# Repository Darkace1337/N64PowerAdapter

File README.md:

# N64PowerAdapter

A modern, universal replacement power supply for the Nintendo 64 using readily available, high-quality power modules.

This project includes the PCB design, schematic, and 3D-printable enclosure required to build a replacement for the original Nintendo 64 power supply. The supply accepts universal AC mains through an IEC C8 connector and provides the 12 V and 3.3 V rails required by the N64 through the original 6-pin power connector.

The design uses TRACO Power modules for the AC/DC and DC/DC conversion, keeping the power circuitry simple while providing an isolated and compact replacement for aging original power supplies.

## Requirements

**A sacrificial Nintendo 64 power adapter (official or third-party) is required for the original 6-pin console connector.**

The connector must be removed from the donor power supply and installed onto the replacement PCB.

## Bill of Materials

| Reference | Qty | Manufacturer | Part Number | Description |
|:---|---:|:---|:---|:---|
| PS1 | 1 | TRACO Power | TEL 10-2410WI | 10 W isolated DC/DC converter, 9–36 V input, 3.3 V / 2.7 A output |
| PS2 | 1 | TRACO Power | TMPW 25-112 | 25 W AC/DC converter, 12 V / 2.083 A output |
| C1 | 1 | KYOCERA AVX | TAJD476K025SNJ | 47 µF, 25 V, 10% tantalum capacitor |
| C2, C4 | 2 | Vishay | 05007-BR104AKU-J | 0.1 µF, 25 V, 10% MLCC |
| C5 | 1 | Vishay | 592D477X96R3C2T20H | 470 µF, 6.3 V, 10% tantalum capacitor |
| F1 | 1 | Eaton | C310T-SC-2-5-R-TR1 | 2.5 A, 250 V ceramic cartridge fuse |
| J1 | 1 | — | Amazon | C8 Panel Mount Plug, flange mount type |
| J3 | 1 | Nintendo / Donor PSU | — | Original N64 6-pin power connector |
| Screws-A | 3 | - | Amazon | M3 x 5 mm Button-head machine screws
| Screws-B | 4 | - | Amazon | M3 x 6 mm Countersunk self tapping screws
| Thread Inserts| 2 | - | Amazon | M3 x 4 mm Heat-set insets

## Project Files

* Schematic and PCB design
* Gerber/manufacturing files
* 3D-printable enclosure
* Reference photos of the assembled prototype

## Prototype / Revision Note

**The photos shown below are of an earlier prototype revision.**

The PCB used in the photographed prototype required a small section of the board to be manually cut for proper mechanical fitment. The PCB layout has since been revised to correct this interference.

The current revision is intended to fit without this modification, but has not yet been physically verified in the same configuration shown in the photos.

## Photos

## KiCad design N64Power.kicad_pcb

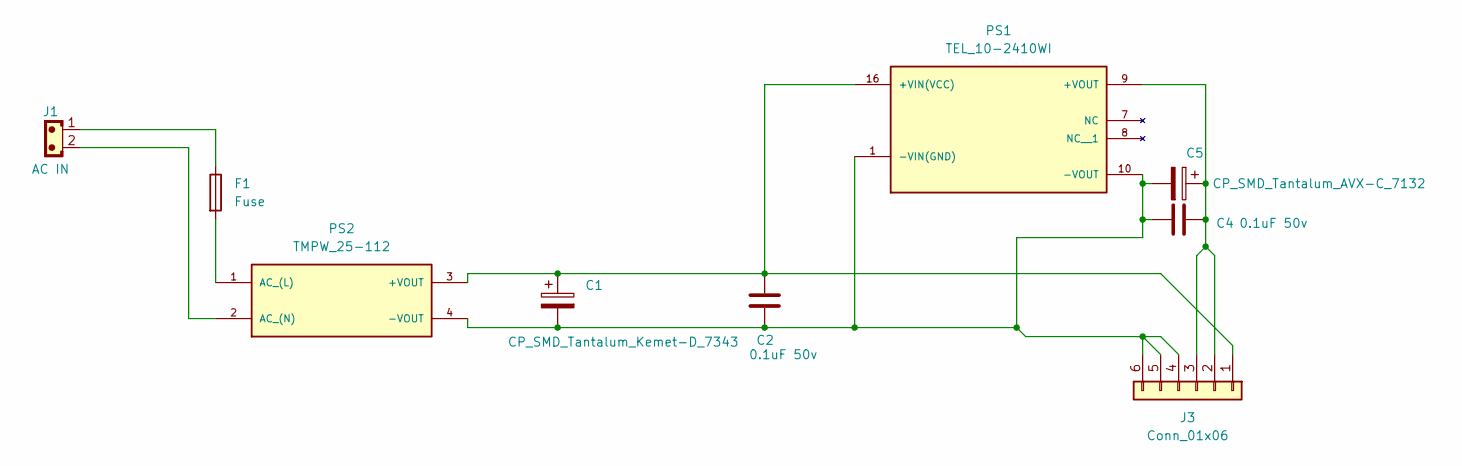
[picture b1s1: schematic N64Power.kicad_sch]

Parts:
C1: CP_SMD_Tantalum_Kemet-D_7343; CP_EIA-7343-31_Kemet-D
C2, C4: 0.1uF 50v; C_1206_3216Metric_Pad1.33x1.80mm_HandSolder
C5: CP_SMD_Tantalum_AVX-C_7132; CP_EIA-7132-28_AVX-C
F1: Fuse; FUSE_0683G2500-01
J1: AC IN; SolderWire-0.75sqmm_1x02_P4.8mm_D1.25mm_OD2.3mm
J3: Conn_01x06; n64ribbon
PS1: TEL_10-2410WI; CONV_TEL_10-2410WI; PARTREV June 16, 2021
PS2: TMPW_25-112; CONV_TMPW_25-112; PARTREV April 20,2021

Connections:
+3.3V: C4.2, C5.1, J3.2, J3.3, PS1.9 (+VOUT)
+12V: C1.1, C2.1, J3.1, PS1.16 (+VIN(VCC)), PS2.3 (+VOUT)
GND: C1.2, C2.2, C4.1, C5.2, J3.4, J3.5, J3.6, PS1.1 (-VIN(GND)), PS1.10 (-VOUT), PS2.4 (-VOUT)
unnamed: F1.1, J1.1
unnamed: F1.2, PS2.1 (AC_(L))
V-L: J1.2, PS2.2 (AC_(N))

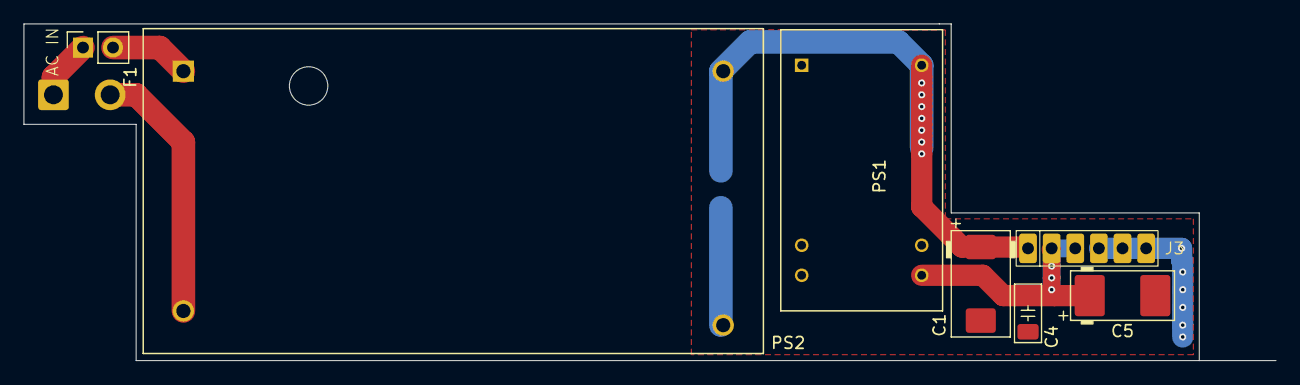
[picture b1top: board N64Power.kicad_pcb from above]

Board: 2 copper layers, 106.0 x 28.5 mm, 9 parts (1 on the bottom side), 6 nets.
